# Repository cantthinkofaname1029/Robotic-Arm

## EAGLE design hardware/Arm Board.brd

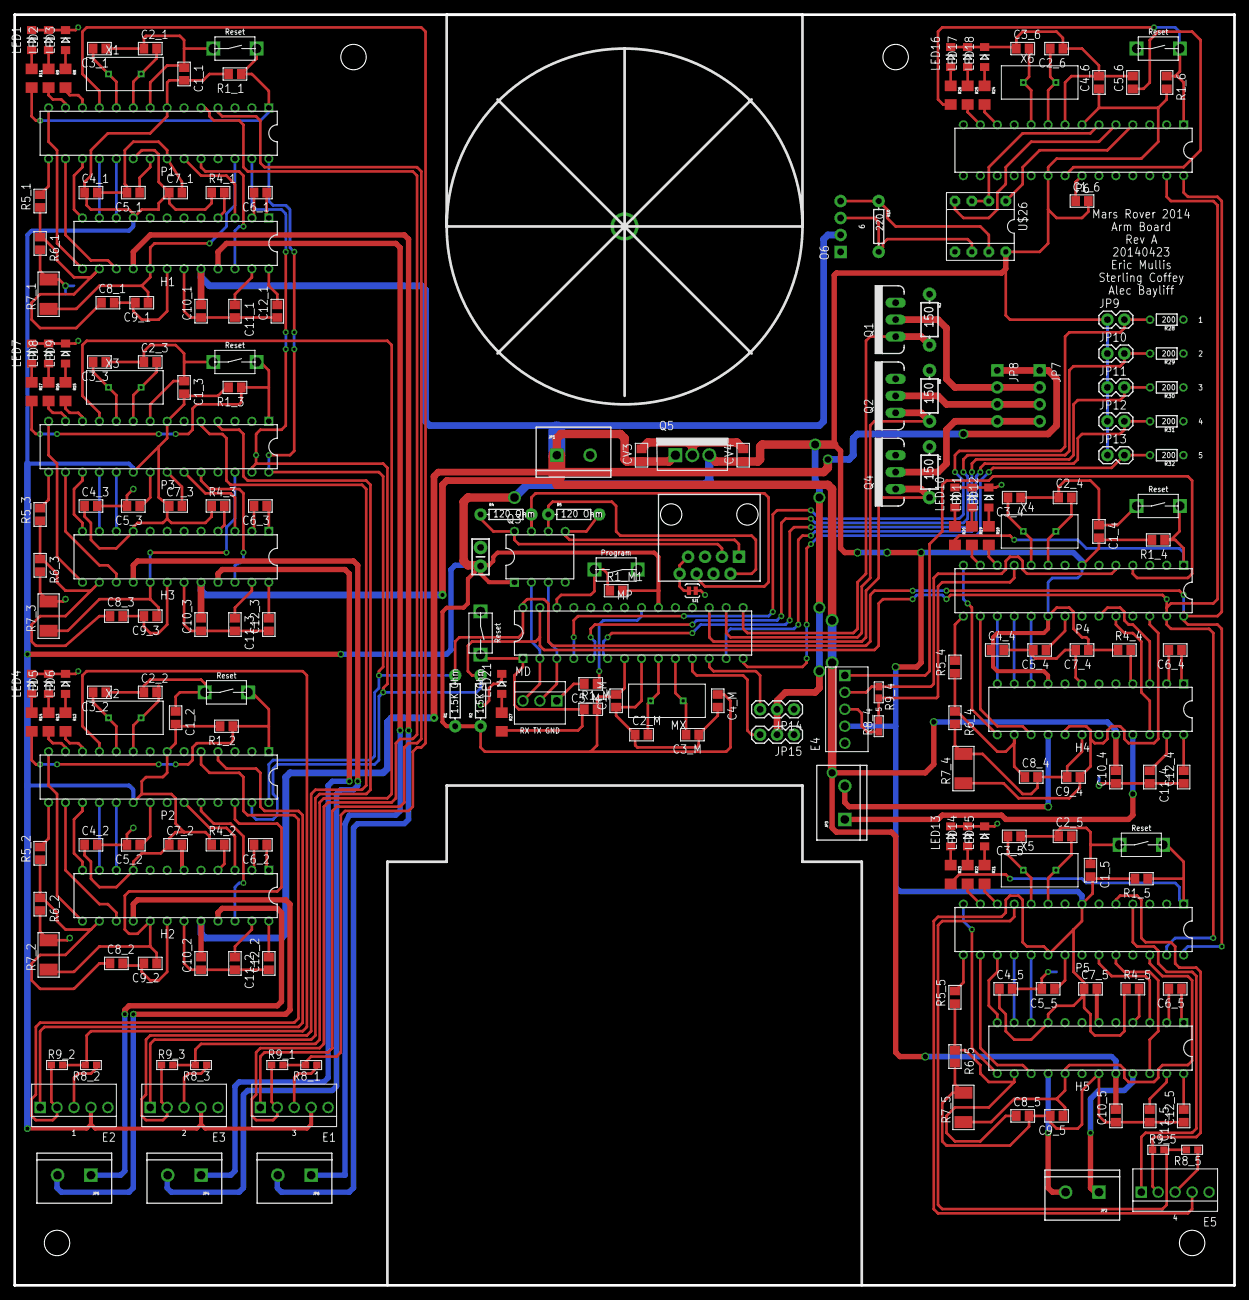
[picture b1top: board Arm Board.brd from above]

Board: 2 copper layers, 182.9 x 190.5 mm, 219 parts (0 on the bottom side), 195 nets.

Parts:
C1_1, C1_2, C1_3, C1_4, C1_5, C1_6, C1_M, C4_1, C4_2, C4_3, C4_4, C4_5, C4_6, C4_M, C5_1, C5_2, C5_3, C5_4, C5_5, C5_6, C5_M, C7_1, C7_2, C7_3, C7_4, C7_5, C8_1, C8_2, C8_3, C8_4, C8_5: .1uF; C_0805
C2_1, C2_2, C2_3, C2_4, C2_5, C2_6, C2_M, C3_1, C3_2, C3_3, C3_4, C3_5, C3_6, C3_M: 15pF; C_0805
C6_1, C6_2, C6_3, C6_4, C6_5: 0.22uF; C_0805
C9_1, C9_2, C9_3, C9_4, C9_5: C_0805
C10: .1uF; CAP-PTH-SMALL-KIT
C10_1, C10_2, C10_3, C10_4, C10_5: 1uF; C_0805
C11_1, C11_2, C11_3, C11_4, C11_5, C12_1, C12_2, C12_3, C12_4, C12_5: .22uF; C_0805
CV3, CV4: .1uF; C_0805
E1, E2, E3, E4, E5: J_MTA100_5P
H1, H2, H3, H4, H5: A3959; DIP24
J6: J_MC32857; J_TOGGLE
JP1, JP2, JP3, JP4, JP5, JP6: M025MM; SCREWTERMINAL-5MM-2
JP7, JP8: 1X04_NO_SILK
JP9, JP10, JP11, JP12, JP13: M02PTH; 1X02
JP14, JP15: 1X03
LED1, LED2, LED3, LED4, LED5, LED6, LED7, LED8, LED9, LED10, LED11, LED12, LED13, LED14, LED15, LED16, LED17, LED18, LED21: LED-1206
MD: J_MTA100_3P
MP: ATMEGA328P; DIP28
MS, MS1: J_MC32857; J_TOGGLE
MX: HC49S; HC-49
O6: 1X04_NO_SILK
P1, P2, P3, P4, P5, P6: ATMEGA328P; DIP28
Q1, Q2, Q4: MOSFET-NCHANNELFQP30N06L; TO220V
Q3: Q_LTC490; DIP8
Q5: LDO; TO-220
R1, R2: 1.5K Ohm; AXIAL-0.3
R1_1, R1_2, R1_3, R1_4, R1_5, R1_6, R1_M, R1_M1: 200; R_0805
R3, R6, R7: 150; AXIAL-0.3-KIT
R4, R5: 120 Ohm; AXIAL-0.3
R4_1, R4_2, R4_3, R4_4, R4_5: 51k; R_0805
R5_1, R5_2, R5_3, R5_4, R5_5: 1k; R_0805
R6_1, R6_2, R6_3, R6_4, R6_5: 10k; R_0805
R7_1: .1; R_2010
R7_2, R7_3, R7_4, R7_5: R_2010
R8, R9, R11, R12, R13, R14, R15, R16, R17, R18, R19, R20, R21, R22, R23, R24, R25, R26, R27: 120; 1206
R8_1, R8_2, R8_3, R8_4, R8_5, R9_1, R9_2, R9_3, R9_4, R9_5: 0; R_0603
R10: 220; AXIAL-0.3EZ
R28, R29, R30, R31, R32: 200; 1/6W-RES
S1, S2, S3, S4, S5: J_MC32857; J_TOGGLE
SJ1: SOLDERJUMPERTRACE; SJ_2S-TRACE
U$2: RJ45-8PTH; RJ45-8
U$26: MAX485DIL; DIL08
X1, X2, X3, X4, X5, X6: HC49S; HC-49

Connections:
B1: JP9.2, MP.4, R28.2
B2: JP10.2, MP.5, R29.2
B3: JP11.2, MP.6, R30.2
B4: JP12.2, MP.13, R31.2
B5: JP13.2, MP.14, R32.2
BLANK1: H1.12, P1.17
BLANK2: H2.12, P2.17
BLANK3: H3.12, P3.17
BLANK4: H4.12, P4.17
BLANK5: H5.12, P5.17
D+: O6.3, R10.P$2, U$26.6
D-: O6.4, R10.P$1, U$26.7
DIR6: P6.6, U$26.2, U$26.3
DM: MD.2, MP.3, Q3.3
EN1: H1.10, P1.19
EN2: H2.10, P2.19
EN3: H3.10, P3.19
EN4: H4.10, P4.19
EN5: H5.10, P5.19
EXTMODE1: H1.15, P1.16
EXTMODE2: H2.15, P2.16
EXTMODE3: H3.15, P3.16
EXTMODE4: H4.15, P4.16
EXTMODE5: H5.15, P5.16
GND: C1_1.1, C1_2.1, C1_3.1, C1_4.1, C1_5.1, C1_6.1, C1_M.1, C2_1.1, C2_2.1, C2_3.1, C2_4.1, C2_5.1, C2_6.1, C2_M.1, C3_1.1, C3_2.1, C3_3.1, C3_4.1, C3_5.1, C3_6.1, C3_M.1, C4_1.2, C4_2.2, C4_3.2, C4_4.2, C4_5.2, C4_6.2, C4_M.2, C5_1.2, C5_2.2, C5_3.2, C5_4.2, C5_5.2, C5_6.2, C5_M.2, C7_1.2, C7_2.2, C7_3.2, C7_4.2, C7_5.2, C8_1.2, C8_2.2, C8_3.2, C8_4.2, C8_5.2, C9_1.2, C9_2.2, C9_3.2, C9_4.2, C9_5.2, C10.2, C10_1.1, C10_2.1, C10_3.1, C10_4.1, C10_5.1, C11_1.2, C11_2.2, C11_3.2, C11_4.2, C11_5.2, C12_1.1, C12_2.1, C12_3.1, C12_4.1, C12_5.1, CV3.2, CV4.2, E1.5, E2.5, E3.5, E4.5, E5.5, H1.5, H1.6, H1.7, H1.8, H1.18, H1.19, H2.5, H2.6, H2.7, H2.8, H2.18, H2.19, H3.5, H3.6, H3.7, H3.8, H3.18, H3.19, H4.5, H4.6, H4.7, H4.8, H4.18, H4.19, H5.5, H5.6, H5.7, H5.8, H5.18, H5.19, J6.P$1, JP1.2, JP14.1, JP15.1, LED1.C, LED2.C, LED3.C, LED4.C, LED5.C, LED6.C, LED7.C, LED8.C, LED9.C, LED10.C, LED11.C, LED12.C, LED13.C, LED14.C, LED15.C, LED16.C, LED17.C, LED18.C, LED21.C, MD.1, MP.8, MP.22, MS.P$1, MS1.P$1, O6.1, P1.8, P1.22, P2.8, P2.22, P3.8, P3.22, P4.8, P4.22, P5.8, P5.22, P6.8, P6.22, Q1.3, Q2.3, Q3.4, Q4.3, Q5.2, R3.P$1, R6.P$1, R6_1.2, R6_2.2, R6_3.2, R6_4.2, R6_5.2, R7.P$1, R7_1.2, R7_2.2, R7_3.2, R7_4.2, R7_5.2, R28.1, R29.1, R30.1, R31.1, R32.1, S1.P$1, S2.P$1, S3.P$1, S4.P$1, S5.P$1, SJ1.1, U$26.5
INTERRUPT1_1: E1.2, P1.5, R9_1.1
INTERRUPT1_2: E2.2, P2.5, R9_2.1
INTERRUPT1_3: E3.2, P3.5, R9_3.1
INTERRUPT1_4: E4.2, P4.5, R9_4.1
INTERRUPT1_5: E5.2, P5.5, R9_5.1
INTERRUPT2_1: E1.1, P1.4
INTERRUPT2_2: E2.1, P2.4
INTERRUPT2_3: E3.1, P3.4
INTERRUPT2_4: E4.1, P4.4
INTERRUPT2_5: E5.1, P5.4
ISENSE1: C9_1.1, H1.17, P1.26, R7_1.1
ISENSE2: C9_2.1, H2.17, P2.26, R7_2.1
ISENSE3: C9_3.1, H3.17, P3.26, R7_3.1
ISENSE4: C9_4.1, H4.17, P4.26, R7_4.1
ISENSE5: C9_5.1, H5.17, P5.26, R7_5.1
LED1_1: P1.12, R8.2
LED1_2: P2.12, R12.2
LED1_3: P3.12, R15.2
LED1_4: P4.12, R18.2
LED1_5: P5.12, R21.2
LED1_6: P6.12, R24.2
LED2_1: P1.13, R9.2
LED2_2: P2.13, R13.2
LED2_3: P3.13, R16.2
LED2_4: P4.13, R19.2
LED2_5: P5.13, R22.2
LED2_6: P6.13, R25.2
unnamed: Q3.8, R4.P$1, U$2.3
unnamed: LED3.A, R8.1
unnamed: LED2.A, R9.1
unnamed: Q3.5, R5.P$2, U$2.1
unnamed: LED1.A, R11.1
unnamed: LED6.A, R12.1
unnamed: SJ1.2, U$2.7, U$2.8
unnamed: Q3.6, R5.P$1, U$2.2
unnamed: Q3.7, R4.P$2, U$2.6
unnamed: C3_1.2, P1.10, X1.P$1
unnamed: C2_1.2, P1.9, X1.P$2
unnamed: LED5.A, R13.1
unnamed: C5_1.1, P1.21
unnamed: P1.1, R1_1.1, R11.2, S1.P$2
unnamed: C6_1.1, H1.1
unnamed: C6_1.2, H1.2
unnamed: H1.4, R4_1.2
unnamed: LED4.A, R14.1
unnamed: C12_1.2, H1.24
unnamed: LED9.A, R15.1
unnamed: C11_1.1, H1.23
unnamed: LED8.A, R16.1
unnamed: LED7.A, R17.1
unnamed: LED12.A, R18.1
unnamed: E1.3, R8_1.1
unnamed: C3_2.2, P2.10, X2.P$1
unnamed: C2_2.2, P2.9, X2.P$2
unnamed: C5_2.1, P2.21
unnamed: P2.1, R1_2.1, R14.2, S2.P$2
unnamed: C6_2.1, H2.1
unnamed: C6_2.2, H2.2
unnamed: H2.4, R4_2.2
unnamed: C12_2.2, H2.24
unnamed: C11_2.1, H2.23
unnamed: LED11.A, R19.1
unnamed: LED10.A, R20.1
unnamed: LED15.A, R21.1
unnamed: E2.3, R8_2.1
unnamed: C3_3.2, P3.10, X3.P$1
unnamed: C2_3.2, P3.9, X3.P$2
unnamed: C5_3.1, P3.21
unnamed: P3.1, R1_3.1, R17.2, S3.P$2
unnamed: C6_3.1, H3.1
unnamed: C6_3.2, H3.2
unnamed: H3.4, R4_3.2
unnamed: C12_3.2, H3.24
unnamed: C11_3.1, H3.23
unnamed: LED14.A, R22.1
unnamed: LED13.A, R23.1
unnamed: LED18.A, R24.1
unnamed: E3.3, R8_3.1
unnamed: C3_4.2, P4.10, X4.P$1
unnamed: C2_4.2, P4.9, X4.P$2
unnamed: C5_4.1, P4.21
unnamed: P4.1, R1_4.1, R20.2, S4.P$2
unnamed: C6_4.1, H4.1
unnamed: C6_4.2, H4.2
unnamed: H4.4, R4_4.2
unnamed: C12_4.2, H4.24
unnamed: C11_4.1, H4.23
unnamed: LED17.A, R25.1
unnamed: LED16.A, R26.1
unnamed: LED21.A, R27.1
unnamed: E4.3, R8_4.1
unnamed: C3_5.2, P5.10, X5.P$1
unnamed: C2_5.2, P5.9, X5.P$2
unnamed: C5_5.1, P5.21
unnamed: P5.1, R1_5.1, R23.2, S5.P$2
unnamed: C6_5.1, H5.1
unnamed: C6_5.2, H5.2
unnamed: H5.4, R4_5.2
unnamed: C12_5.2, H5.24
unnamed: C11_5.1, H5.23
unnamed: MP.26, MS1.P$2, R1_M1.1
unnamed: E5.3, R8_5.1
unnamed: C3_6.2, P6.10, X6.P$1
unnamed: C2_6.2, P6.9, X6.P$2
unnamed: C5_6.1, P6.21
unnamed: C3_M.2, MP.10, MX.P$1
unnamed: C2_M.2, MP.9, MX.P$2
unnamed: C5_M.1, MP.21
unnamed: MP.1, MS.P$2, R1_M.1, R27.2
O1: JP7.2, JP8.2, Q1.2
O2: JP7.3, JP8.3, Q2.2
O3: JP7.4, JP8.4, Q4.2
OUTA1: H1.16, JP6.2
OUTA2: H2.16, JP5.2
OUTA3: H3.16, JP4.2
OUTA4: H4.16, JP3.2
OUTA5: H5.16, JP2.2
OUTB1: H1.21, JP6.1
OUTB2: H2.21, JP5.1
OUTB3: H3.21, JP4.1
OUTB4: H4.21, JP3.1
OUTB5: H5.21, JP2.1
PFD1_1: H1.13, P1.14
PFD1_2: H2.13, P2.14
PFD1_3: H3.13, P3.14
PFD1_4: H4.13, P4.14
PFD1_5: H5.13, P5.14
PFD2_1: H1.11, P1.18
PFD2_2: H2.11, P2.18
PFD2_3: H3.11, P3.18
PFD2_4: H4.11, P4.18
PFD2_5: H5.11, P5.18
PHASE1: H1.3, P1.23
PHASE2: H2.3, P2.23
PHASE3: H3.3, P3.23
PHASE4: H4.3, P4.23
PHASE5: H5.3, P5.23
PULSE1: P1.11, R8_1.2, R9_1.2
PULSE2: P2.11, R8_2.2, R9_2.2
PULSE3: P3.11, R8_3.2, R9_3.2
PULSE4: P4.11, R8_4.2, R9_4.2
PULSE5: P5.11, R8_5.2, R9_5.2
PWM1: JP15.3, MP.11
PWM2: JP14.3, MP.12
REF1: C8_1.1, H1.14, R5_1.1, R6_1.1
REF1_1: P1.15, R5_1.2
REF1_2: P2.15, R5_2.2
REF1_3: P3.15, R5_3.2
REF1_4: P4.15, R5_4.2
REF1_5: P5.15, R5_5.2
REF2: C8_2.1, H2.14, R5_2.1, R6_2.1
REF3: C8_3.1, H3.14, R5_3.1, R6_3.1
REF4: C8_4.1, H4.14, R5_4.1, R6_4.1
REF5: C8_5.1, H5.14, R5_5.1, R6_5.1
RM: MD.3, MP.2, Q3.2
S1: MP.15, Q1.1, R3.P$2
S2: MP.16, Q2.1, R6.P$2
S3: MP.17, Q4.1, R7.P$2
S6: J6.P$2, P6.1, R1_6.1, R26.2
SCL: MP.28, P1.28, P2.28, P3.28, P4.28, P5.28, P6.28, R1.P$2
SD6: P6.5, U$26.4
SDA: MP.27, P1.27, P2.27, P3.27, P4.27, P5.27, P6.27, R2.P$2
SLEEP1_1: H1.22, P1.24
SLEEP1_2: H2.22, P2.24
SLEEP1_3: H3.22, P3.24
SLEEP1_4: H4.22, P4.24
SLEEP1_5: H5.22, P5.24
SR6: P6.4, U$26.1
V5: C1_1.2, C1_2.2, C1_3.2, C1_4.2, C1_5.2, C1_6.2, C1_M.2, C4_1.1, C4_2.1, C4_3.1, C4_4.1, C4_5.1, C4_6.1, C4_M.1, C7_1.1, C7_2.1, C7_3.1, C7_4.1, C7_5.1, C10.1, CV4.1, E1.4, E2.4, E3.4, E4.4, E5.4, H1.9, H2.9, H3.9, H4.9, H5.9, JP9.1, JP10.1, JP11.1, JP12.1, JP13.1, JP14.2, JP15.2, MP.7, MP.20, P1.7, P1.20, P2.7, P2.20, P3.7, P3.20, P4.7, P4.20, P5.7, P5.20, P6.7, P6.20, Q3.1, Q5.3, R1.P$1, R1_1.2, R1_2.2, R1_3.2, R1_4.2, R1_5.2, R1_6.2, R1_M.2, R1_M1.2, R2.P$1, R4_1.1, R4_2.1, R4_3.1, R4_4.1, R4_5.1, U$26.8
VIN: C10_1.2, C10_2.2, C10_3.2, C10_4.2, C10_5.2, CV3.1, H1.20, H2.20, H3.20, H4.20, H5.20, JP1.1, JP7.1, JP8.1, O6.2, Q5.1

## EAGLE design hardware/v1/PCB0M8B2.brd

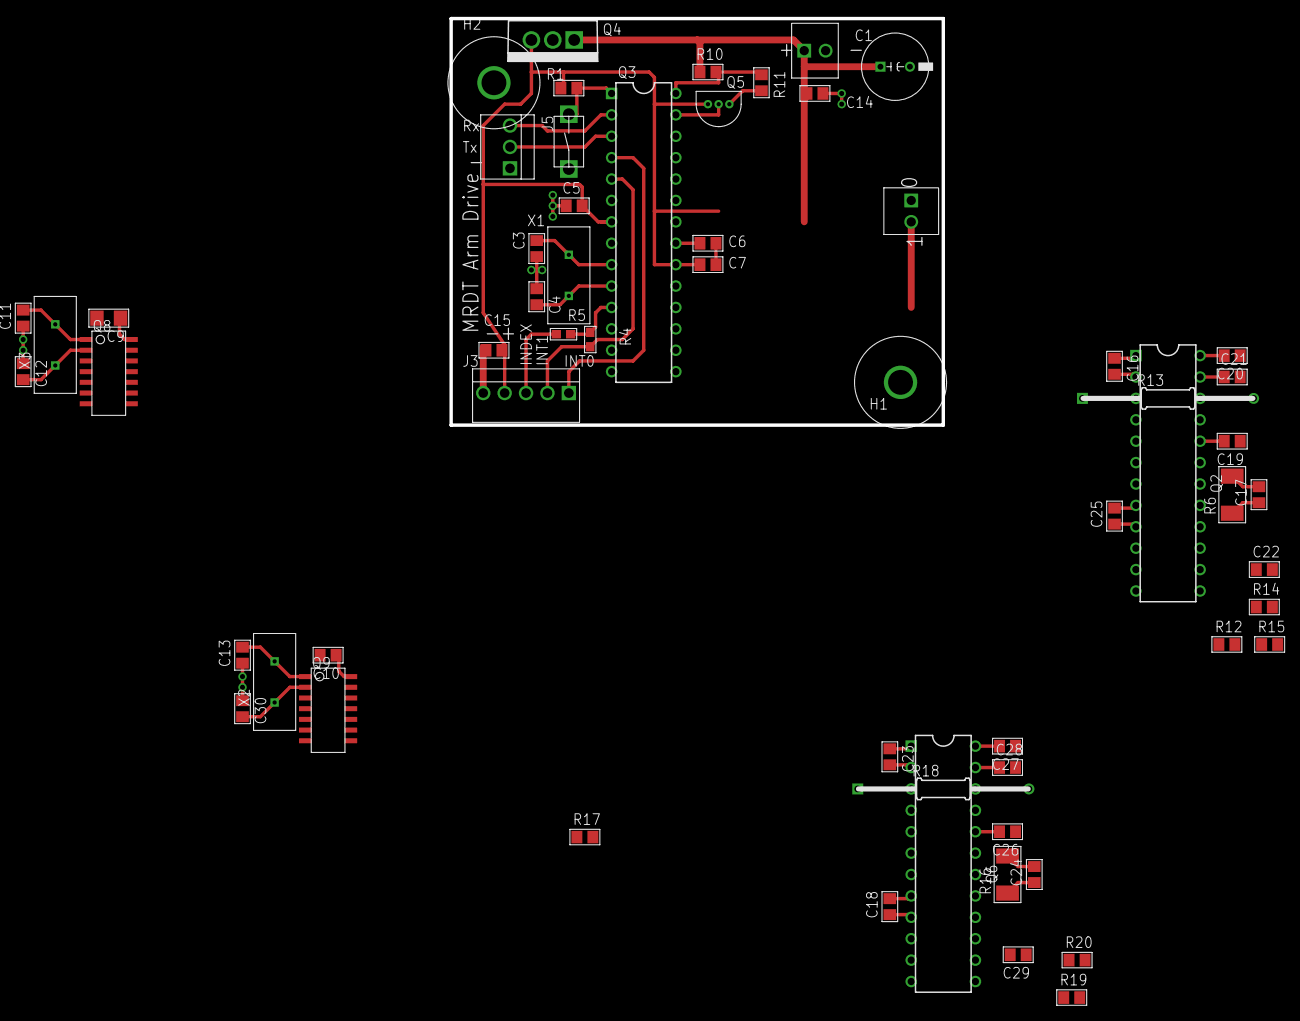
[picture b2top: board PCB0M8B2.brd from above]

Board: 2 copper layers, 58.4 x 48.3 mm, 60 parts (0 on the bottom side), 40 nets.

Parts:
C1: 330uF; C_8MM
C3: 15pF; C_0805
C4, C5, C6, C7, C10, C11, C12, C13, C14, C15, C17, C18, C19, C20, C21, C24, C25, C26, C27, C28, C30: C_0805
C9: C_1206
C16, C23: 0.22uF; C_0805
C22, C29: 0.1uF; C_0805
H1, H2: H_MNTHOLE_#4
J1, J2: J_1546074-2282834-2; J_2.54MM
J3: J_MTA100_5P
J4: J_MC32857; J_TOGGLE
J5: J_MTA100_3P
Q2, Q6: A3959; DIP24
Q3: ATMEGA328P; DIP28
Q4: LDO; TO-220
Q5: LM35; TO-92-3
Q8, Q9: Q_LFLS7366R-S; SOIC14
R1: 200; R_0805
R4, R5: R_0603
R6, R16: R_2010
R10, R11: R_0805
R12, R17: 51k; R_0805
R13, R18: R_1/4WL
R14, R19: 10k; R_0805
R15, R20: 1k; R_0805
X1: HC49S; HC-49
X2, X3: X_HC49SCRYSTAL; HC-49

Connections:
D: J5.2, Q3.3
GND: C1.-, C3.1, C4.1, C5.1, C6.2, C7.2, C9.2, C10.2, C11.1, C12.1, C13.1, C14.2, C15.2, C17.2, C18.2, C19.1, C20.1, C21.2, C22.2, C24.2, C25.2, C26.1, C29.2, C30.1, J1.P$2, J3.5, J4.P$1, J5.1, Q2.5, Q2.6, Q2.7, Q2.8, Q2.18, Q2.19, Q3.8, Q3.22, Q4.2, Q5.1, Q6.5, Q6.6, Q6.7, Q6.8, Q6.18, Q6.19, Q8.3, Q9.3, R6.2, R11.2, R14.2, R16.2, R19.2
INTERRUPT1: J3.2, Q3.5, R4.1
INTERRUPT2: J3.1, Q3.4
ISENSE: C17.1, C24.1, Q3.26, R6.1, R16.1
unnamed: C4.2, Q3.10, X1.P$1
unnamed: C3.2, Q3.9, X1.P$2
unnamed: C9.1, Q8.14
unnamed: Q3.27, Q5.2
unnamed: Q3.28, R10.2, R11.1
unnamed: C6.1, Q3.21
unnamed: J3.3, R5.1
unnamed: J4.P$2, Q3.1, R1.1
unnamed: C10.1, Q9.14
unnamed: C12.2, Q8.2, X3.P$1
unnamed: C16.1, Q2.1
unnamed: C16.2, Q2.2
unnamed: C11.2, Q8.1, X3.P$2
unnamed: Q2.4, R12.2
unnamed: C20.2, Q2.24
unnamed: C21.1, Q2.23
unnamed: Q2.22, R13.2
unnamed: C23.1, Q6.1
unnamed: C13.2, Q9.1, X2.P$2
unnamed: C23.2, Q6.2
unnamed: C30.2, Q9.2, X2.P$1
unnamed: Q6.4, R17.2
unnamed: C27.2, Q6.24
unnamed: C28.1, Q6.23
unnamed: Q6.22, R18.2
unnamed: C27.1, C28.2
OUTB: J2.P$1, Q6.21
PULSE: Q3.11, R4.2, R5.2
R: J5.3, Q3.2
REF2: C22.1, Q2.14, R14.1, R15.1
REF3: C29.1, Q6.14, R19.1, R20.1
V5: C5.2, C7.1, C15.1, C18.1, C25.1, J3.4, Q2.9, Q3.7, Q3.20, Q4.3, Q5.3, Q6.9, R1.2, R12.1, R17.1
VIN: C1.+, C14.1, J1.P$1, Q4.1, R10.1
VIN1: C19.2, Q2.20
VIN2: C26.2, Q6.20

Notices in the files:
parts and their libraries:
SparkFun-DigitalIC: Licensing: CC v3.0 Share-Alike You are welcome to use this library for commercial purposes.
LilyPad-Wearables: Licensing:Creative Commons ShareAlike 4.0 International - https://creativecommons.org/licenses/by-sa/4.0
